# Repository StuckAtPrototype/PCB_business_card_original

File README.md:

# Original business card - StuckAtPrototype

A custom PCB based "business" card that lets you play a version of Flappy Bird.

## Youtube Video
A bit of a back-story of how this project came to be.

Sub if you like what you see.

## Project Structure
The project consists of
1. Firmware
2. Hardware

## Firmware
You will need to set up the environment from scratch. You can use any method youd like, but the method mentioned below is probably the easiest.

### Compilation
You will need to obtain chip related code. The "API" from NXP. This comes with Keil uVision. I recommend using it for simplicity. 

The chip is MKE04Z4

# Hardware
I am including everything youd need to make one of these. 

---
## License
### Apache 2.0 -- i.e. use as you'd like
http://www.apache.org/licenses/LICENSE-2.0

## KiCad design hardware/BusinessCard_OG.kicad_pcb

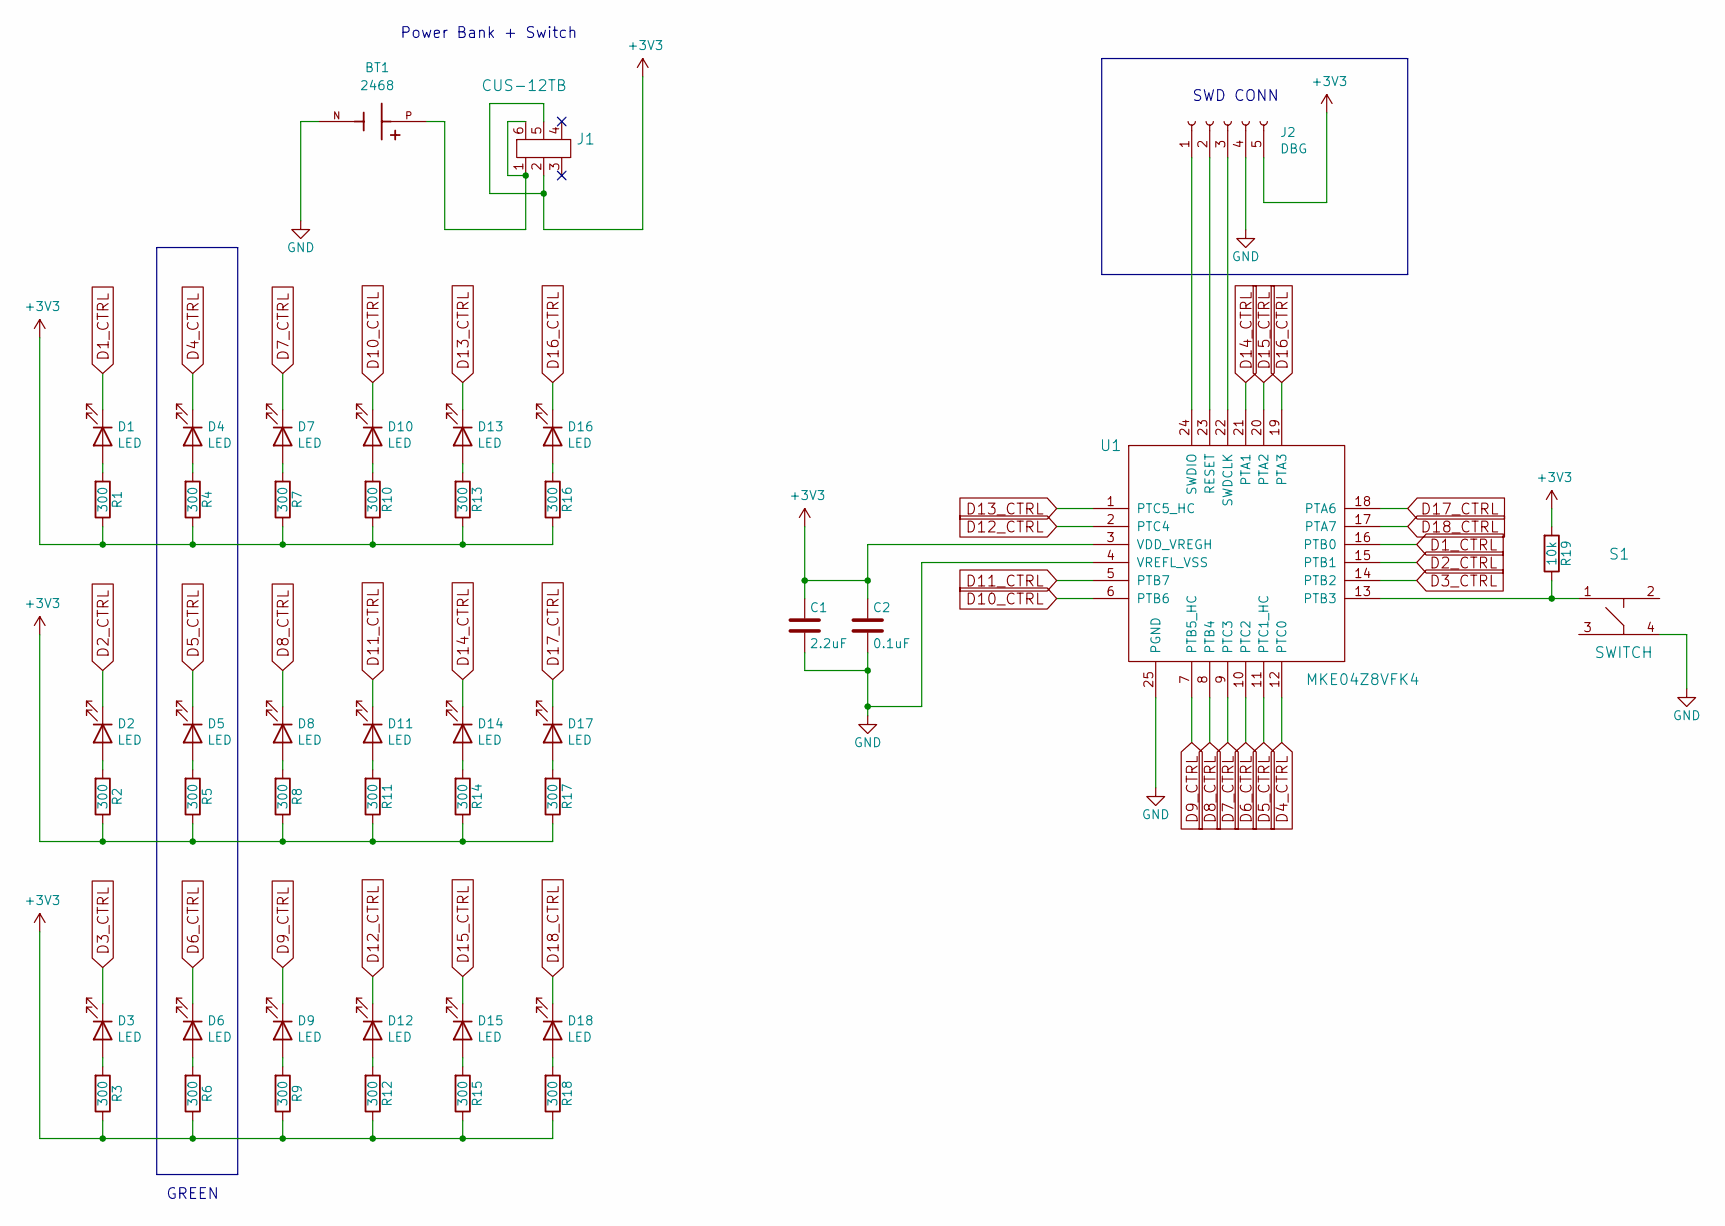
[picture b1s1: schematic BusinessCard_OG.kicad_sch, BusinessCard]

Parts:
BT1: 2468; BAT_2468; PARTREV D
C1: 2.2uF; C_0603_1608Metric
C2: 0.1uF; C_0603_1608Metric
D1, D2, D3, D4, D5, D6, D7, D8, D9, D10, D11, D12, D13, D14, D15, D16, D17, D18: LED; LED_0603_1608Metric
J1: CUS-12TB; JS202011AQN
J2: DBG; PinHeader_1x05_P1.27mm_Vertical
R1, R2, R3, R4, R5, R6, R7, R8, R9, R10, R11, R12, R13, R14, R15, R16, R17, R18: 300; R_0603_1608Metric
R19: 10k; R_0603_1608Metric
S1: SWITCH; 6mm_tac_switch
U1: MKE04Z8VFK4; QFN-24_4x4_05_test

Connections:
+3V3: C1.1, C2.1, J1.2, J1.5, J2.5, R1.1, R2.1, R3.1, R4.1, R5.1, R6.1, R7.1, R8.1, R9.1, R10.1, R11.1, R12.1, R13.1, R14.1, R15.1, R16.1, R17.1, R18.1, R19.2, U1.3 (VDD_VREGH)
D1_CTRL: D1.1 (K), U1.16 (PTB0)
D2_CTRL: D2.1 (K), U1.15 (PTB1)
D3_CTRL: D3.1 (K), U1.14 (PTB2)
D4_CTRL: D4.1 (K), U1.12 (PTC0)
D5_CTRL: D5.1 (K), U1.11 (PTC1_HC)
D6_CTRL: D6.1 (K), U1.10 (PTC2)
D7_CTRL: D7.1 (K), U1.9 (PTC3)
D8_CTRL: D8.1 (K), U1.8 (PTB4)
D9_CTRL: D9.1 (K), U1.7 (PTB5_HC)
D10_CTRL: D10.1 (K), U1.6 (PTB6)
D11_CTRL: D11.1 (K), U1.5 (PTB7)
D12_CTRL: D12.1 (K), U1.2 (PTC4)
D13_CTRL: D13.1 (K), U1.1 (PTC5_HC)
D14_CTRL: D14.1 (K), U1.21 (PTA1)
D15_CTRL: D15.1 (K), U1.20 (PTA2)
D16_CTRL: D16.1 (K), U1.19 (PTA3)
D17_CTRL: D17.1 (K), U1.18 (PTA6)
D18_CTRL: D18.1 (K), U1.17 (PTA7)
GND: BT1.N, C1.2, C2.2, J2.4, S1.4, U1.4 (VREFL_VSS), U1.25 (PGND)
unnamed: BT1.P, J1.1, J1.6
unnamed: D1.2 (A), R1.2
unnamed: D2.2 (A), R2.2
unnamed: D3.2 (A), R3.2
unnamed: D4.2 (A), R4.2
unnamed: D5.2 (A), R5.2
unnamed: D6.2 (A), R6.2
unnamed: D7.2 (A), R7.2
unnamed: D8.2 (A), R8.2
unnamed: D9.2 (A), R9.2
unnamed: D10.2 (A), R10.2
unnamed: D11.2 (A), R11.2
unnamed: D12.2 (A), R12.2
unnamed: D13.2 (A), R13.2
unnamed: D14.2 (A), R14.2
unnamed: D15.2 (A), R15.2
unnamed: D16.2 (A), R16.2
unnamed: D17.2 (A), R17.2
unnamed: D18.2 (A), R18.2
unnamed: J2.1, U1.24 (SWDIO)
unnamed: J2.2, U1.23 (RESET)
unnamed: J2.3, U1.22 (SWDCLK)
unnamed: R19.1, S1.1, U1.13 (PTB3)

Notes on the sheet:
SWD CONN
GREEN
Power Bank + Switch

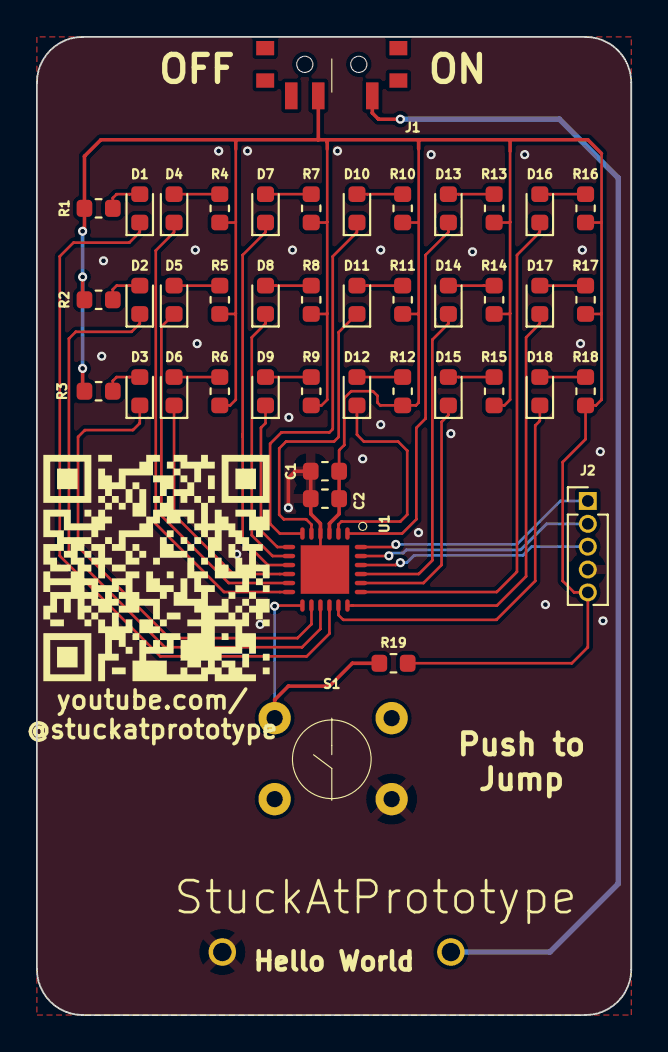
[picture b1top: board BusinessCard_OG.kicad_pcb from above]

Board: 4 copper layers, 33.0 x 54.3 mm, 44 parts (1 on the bottom side), 43 nets.

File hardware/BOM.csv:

Id,Designator,Footprint,Quantity,Designation,Supplier and ref,
1,C1,C_0603_1608Metric,1,2.2uF,CL10A225KO8NNNC,
2,"R1,R2,R4,R18,R8,R3,R5,R6,R7,R9,R10,R11,R12,R13,R14,R15,R16,R17",R_0603_1608Metric,18,300,ESR03EZPF4700,Note: changed to 470
3,U1,QFN-24_4x4_05_test,1,MKE04Z8VFK4,MKE04Z8VFK4,
4,S1,6mm_tac_switch,1,SWITCH,B3F-1000 ,Note: 6mm switch
5,C2,C_0603_1608Metric,1,0.1uF,CC0603KRX7R7BB104,
6,J1,JS202011AQN,1,JS202011AQN,JS202011AQN,
7,"D1,D2,D3,D7,D8,D9,D10,D11,D12,D13,D14,D15,D16,D17,D18",LED_0603_1608Metric,15,LED,150060RS75000,Note: RED
8,"D4,D5,D6",LED_0603_1608Metric,3,LED,150060GS75000,Note: Green
9,R19,R_0603_1608Metric,1,10k,WR06X103 JTL,
10,BT1,BAT_2468,1,2468,2468,
